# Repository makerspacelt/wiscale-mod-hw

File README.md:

This is ESP8266 and HX711 based weight monitoring device.

* Designed from commonly available aliexpress modules.
* Supports multiple load cells.
* Can be populated with 18650 battery
* Can be operated in ultra low power mode

Dev NOTE: before commit, run `./kibot.sh` to regenerate documentation, bom, gerbers and other assets.

* [schematics.pdf](gen/schematics.pdf)
* [pcb.pdf with dimensions](gen/pcb.pdf)
* [pcb_bottom.pdf for toner transfer](gen/pcb_bottom.pdf)
* [ibom.html](gen/bom_ibom.html)
* [gerbers.zip](gen/gerbers/gerbers.zip)

## Normal operation

The circuit should be powered via a USB connector on the LiPo charger unless
battery support and low-power sleep is not used.

## Assembly and hardware configuration notes

### LiPo charger

Chargers(U1) with and without protection can be used. To use a charger without
protection that does not have separate power output pins - R1 needs to be
shorted out with a wire or zero ohms resistor.

For applications not requiring batteries whole LiPo charger section can be
omitted including components U1,Q1,BT1,F1,C1,C4,C5,C6. That requires that
the circuit be powered via a USB connector on the WeMos D1 mini module.

### Low-power sleep

A timer is equipped with selectable(SW1) wake-up settings(R11 and R12).

For applications that do not require a low-power sleep timer can be bypassed
by shorting out R14. Optionally components U3,C7,Q2,SW1,R11,R12 can be
omitted in assembly.

### Boost converter for ADC

Tests show that the circuit works down to about 2.7V without the need for
boosting voltage for ADC. Following that - the boost converter(U5) can be
omitted and R16 shorted out to bypass it.

### ADC configuration

To reduce noise on measurements capacitors(C9,C10,C11) on ADC input there
placed. As a side effect, they slow down reading settling time after weight change.
Removing these capacitors will give a fast reading but increase spread
by about 3 times.

Populating all of the R4,R5,R6,R7 links gives the ability to choose an ADC
amplifier and gain purely via software. What are the drawbacks of this
approach are unclear to me but there is an option to disconnect unused
amplifier by removing either R4 and R5 or R6 and R7 links.

## Software notes:

* keep D0 as input at all times for compatibility with older hardware (v1.0).

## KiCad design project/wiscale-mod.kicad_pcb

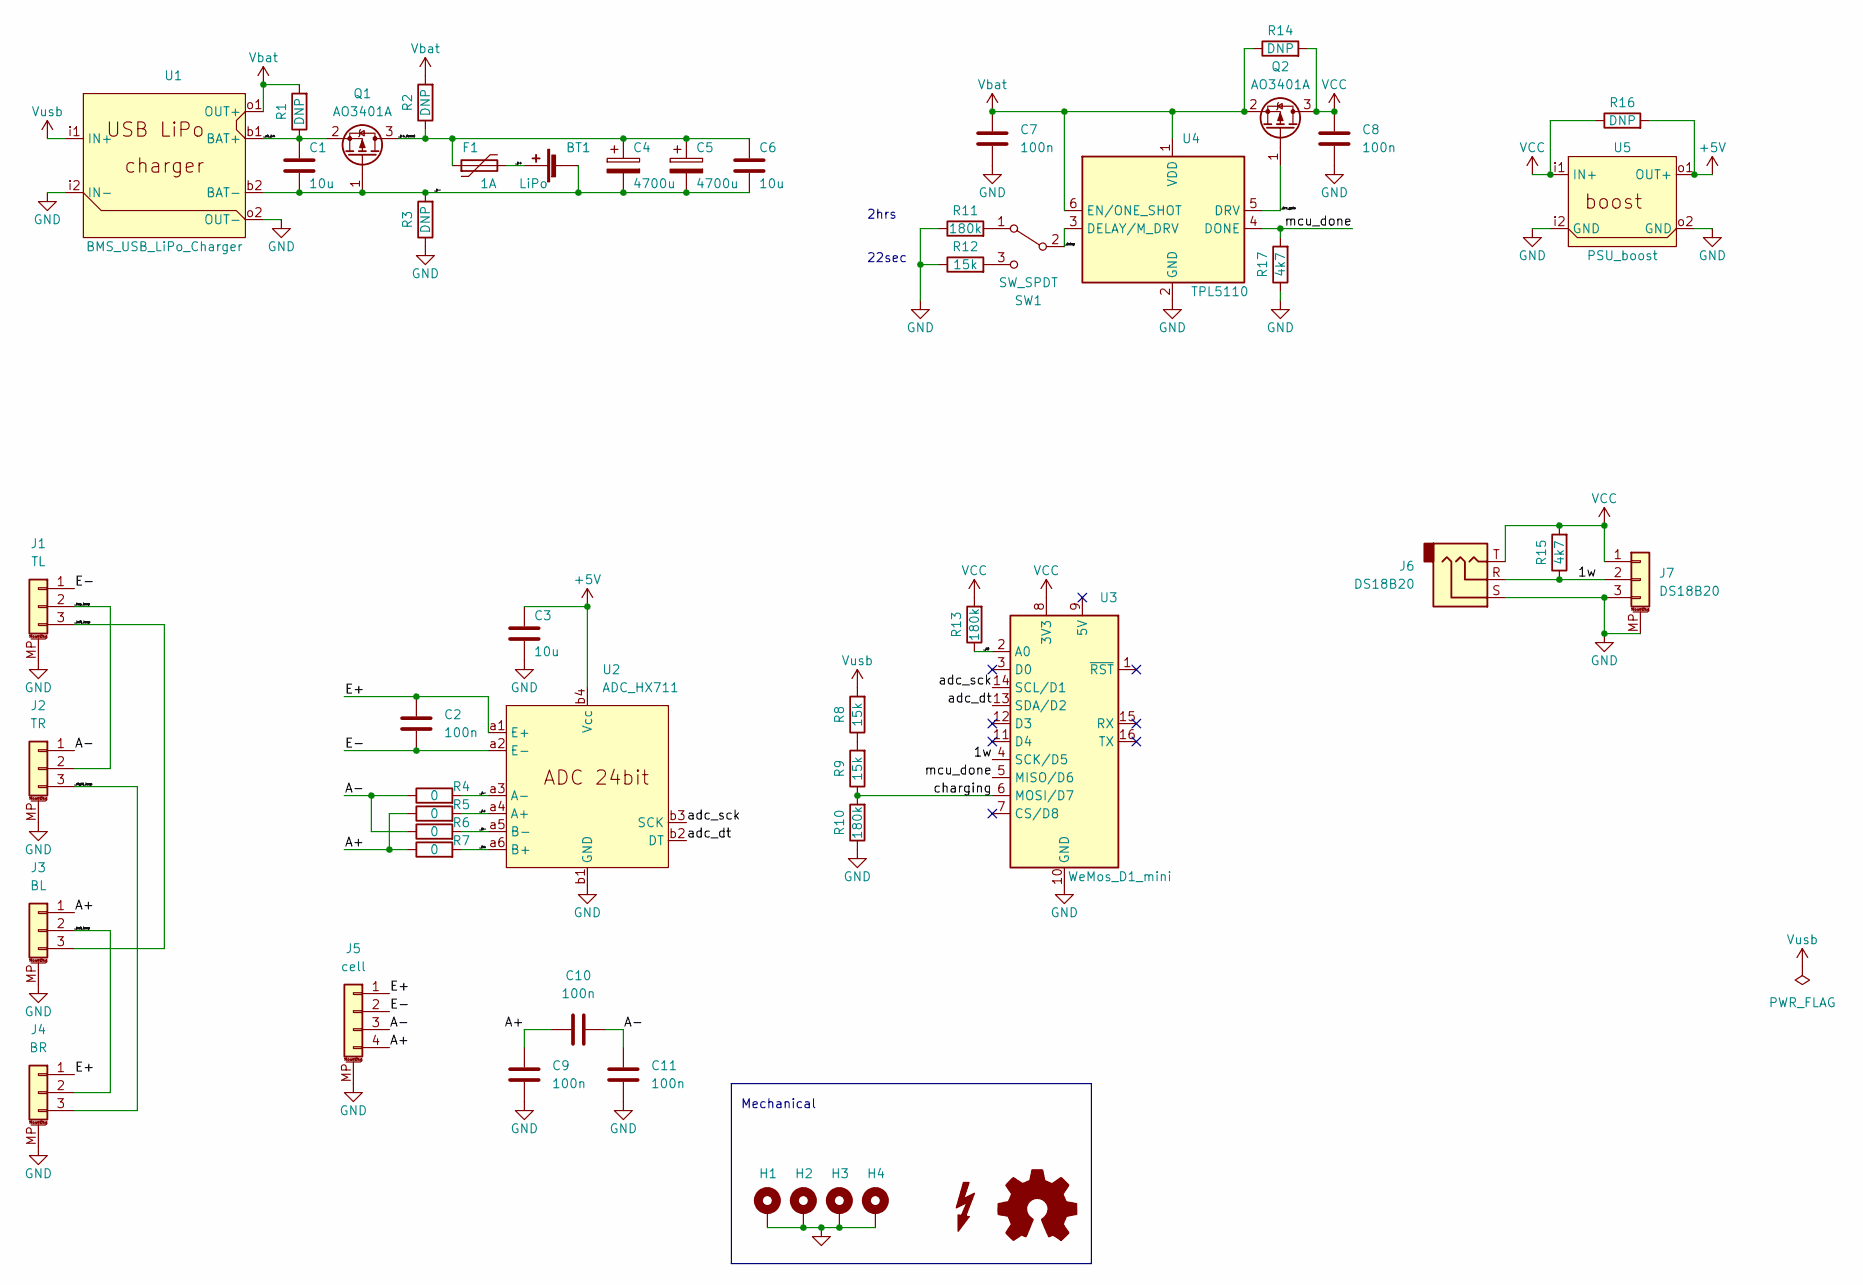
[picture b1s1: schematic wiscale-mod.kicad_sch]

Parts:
BT1: LiPo; BAT_BH-18650-PC
C1, C3, C6: 10u; C_0805_2012Metric_Pad1.18x1.45mm_HandSolder
C2, C7, C8, C9, C10, C11: 100n; C_0805_2012Metric_Pad1.18x1.45mm_HandSolder
C4, C5: 4700u; CP_Radial_D13.0mm_P5.00mm_L26.0mm
F1: 1A; Fuse_1206_3216Metric_Pad1.42x1.75mm_HandSolder
H1, H2, H3, H4: MountingHole_Pad; MountingHole_3.5mm_Pad_Via
J1: TL; JST_XH_S3B-XH-A-1_1x03_P2.50mm_Horizontal
J2: TR; JST_XH_S3B-XH-A-1_1x03_P2.50mm_Horizontal
J3: BL; JST_XH_S3B-XH-A-1_1x03_P2.50mm_Horizontal
J4: BR; JST_XH_S3B-XH-A-1_1x03_P2.50mm_Horizontal
J5: cell; JST_XH_S4B-XH-A-1_1x04_P2.50mm_Horizontal
J6: DS18B20; Jack_3.5mm_Horizontal
J7: DS18B20; JST_XH_S3B-XH-A-1_1x03_P2.50mm_Horizontal
LOGO1: logo_kms_small; logo_kms_small_copper
LOGO2: Logo_Open_Hardware_Small; OSHW-Symbol_6.7x6mm_Copper
Q1, Q2: AO3401A; SOT-23
R1, R2, R3, R14, R16: DNP; R_0805_2012Metric_Pad1.20x1.40mm_HandSolder
R4, R5, R6, R7: 0; R_0805_2012Metric_Pad1.20x1.40mm_HandSolder
R8, R9, R12: 15k; R_0805_2012Metric_Pad1.20x1.40mm_HandSolder
R10, R11, R13: 180k; R_0805_2012Metric_Pad1.20x1.40mm_HandSolder
R15, R17: 4k7; R_0805_2012Metric_Pad1.20x1.40mm_HandSolder
SW1: SW_SPDT; SW_E-Switch_EG1271_DPDT
U1: BMS_USB_LiPo_Charger; module_bms_usb_lipo_charger
U2: ADC_HX711; module_adc_hx711_multi
U3: WeMos_D1_mini; WEMOS_D1_mini_light
U4: TPL5110; SOT-23-6
U5: PSU_boost; module_psu_boost

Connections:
+5V: C3.2, R16.2, U2.b4 (Vcc), U5.o1 (OUT+)
/1w: J6.R, J7.2, R15.1, U3.4 (SCK/D5)
/A+: C9.2, C10.2, J3.1, J5.4, R5.1, R7.1
/A-: C10.1, C11.2, J2.1, J5.3, R4.1, R6.1
/E+: C2.2, J4.1, J5.1, U2.a1 (E+)
/E-: C2.1, J1.1, J5.2, U2.a2 (E-)
/_A0: R13.1, U3.2 (A0)
/_A+: R5.2, U2.a4 (A+)
/_A-: R4.2, U2.a3 (A-)
/_B+: R7.2, U2.a6 (B+)
/_B-: R6.2, U2.a5 (B-)
/_b+: BT1.1 (+), F1.2
/_b+_fused: C4.1, C5.1, C6.2, F1.1, Q1.3 (D), R2.1
/_b-: BT1.2 (-), C1.1, C4.2, C5.2, C6.1, Q1.1 (G), R3.2, U1.b2 (BAT-)
/_ch_b+: C1.2, Q1.2 (S), R1.1, U1.b1 (BAT+)
/_delay: SW1.2 (B), U4.3 (DELAY/M_DRV)
/_drv_gate: Q2.1 (G), U4.5 (DRV)
/adc_dt: U2.b2 (DT), U3.13 (SDA/D2)
/adc_sck: U2.b3 (SCK), U3.14 (SCL/D1)
/charging: R9.1, R10.2, U3.6 (MOSI/D7)
/mcu_done: R17.2, U3.5 (MISO/D6), U4.4 (DONE)
GND: C3.1, C7.1, C8.1, C9.1, C11.1, H1.1, H2.1, H3.1, H4.1, J1.MP (MountPin), J2.MP (MountPin), J3.MP (MountPin), J4.MP (MountPin), J5.MP (MountPin), J6.S, J7.3, J7.MP (MountPin), R3.1, R10.1, R11.1, R12.1, R17.1, U1.i2 (IN-), U1.o2 (OUT-), U2.b1 (GND), U3.10 (GND), U4.2 (GND), U5.i2 (GND), U5.o2 (GND)
unnamed: J1.2, J2.2
unnamed: J1.3, J3.3
unnamed: J2.3, J4.3
unnamed: J3.2, J4.2
unnamed: R8.1, R9.2
unnamed: R11.2, SW1.1 (A)
unnamed: R12.2, SW1.3 (C)
VCC: C8.2, J6.T, J7.1, Q2.3 (D), R13.2, R14.2, R15.2, R16.1, U3.8 (3V3), U5.i1 (IN+)
Vbat: C7.2, Q2.2 (S), R1.2, R2.2, R14.1, U1.o1 (OUT+), U4.1 (VDD), U4.6 (EN/ONE_SHOT)
Vusb: R8.2, U1.i1 (IN+)

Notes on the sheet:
2hrs 22sec
Mechanical

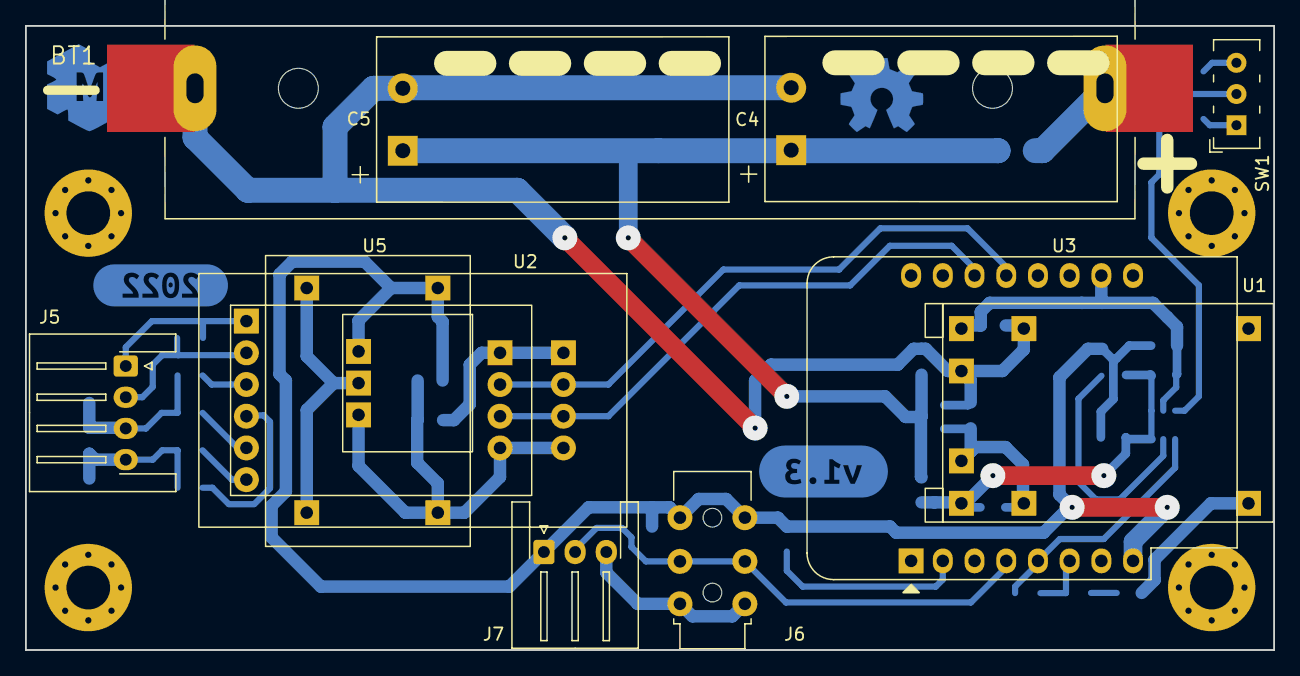
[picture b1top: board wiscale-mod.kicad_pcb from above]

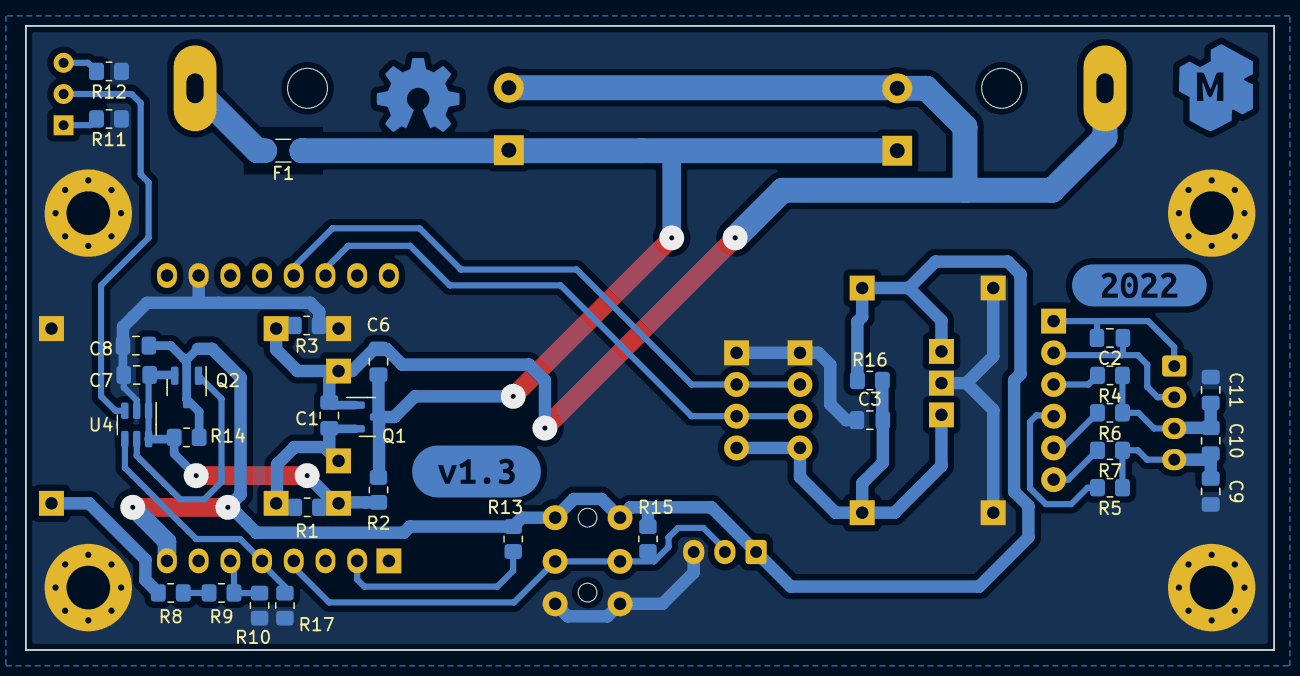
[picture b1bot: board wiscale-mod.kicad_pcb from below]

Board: 2 copper layers, 100.0 x 50.0 mm, 49 parts (34 on the bottom side), 28 nets.

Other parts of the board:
kibuzzard-6343E0DF: G***; kibuzzard-6343E0DF
kibuzzard-6352768B: G***; kibuzzard-6352768B

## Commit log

2022-10-10 full project with completed pcb
2022-10-10 generating all the generatables
2022-10-15 moving thermometer from D0 to D5. fixes #1
2022-10-15 adding pull-down on MCU_DONE pin. fixes #2
2022-10-21 adding caps to ADC input to average out noise
2022-10-21 Adding a lot of info to readme. closes #3
